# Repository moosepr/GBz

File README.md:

# GBz
pi zero based, gameboy style inteface board

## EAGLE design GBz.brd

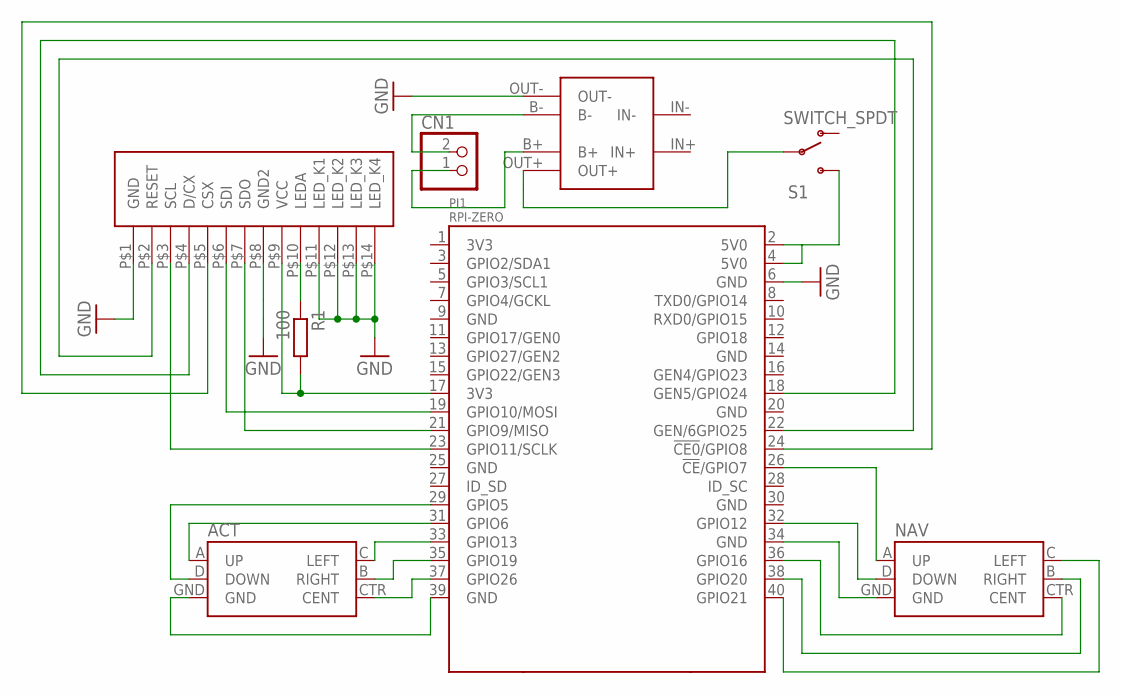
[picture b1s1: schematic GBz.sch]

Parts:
ACT: JOYSTICK_MINI
CN1: JST_2PIN-SMT-RA; JST-PH-2-SMT-RA
NAV: JOYSTICK_MINI
PI1: RPI-ZERO; RASPBERRYPI_BASTELSTUBE_V13_RASPI_BOARD_B+_FULL
POWER1: 03962A
R1: 100; R0805
S1: SWITCH_SPDT; KPS-1290
SCREEN1: ILI9341-2.2

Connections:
5V0@2: PI1.2 (5V0), PI1.4 (5V0), S1.S
GND: PI1.6 (GND), POWER1.OUT-, SCREEN1.P$1 (GND), SCREEN1.P$8 (GND2), SCREEN1.P$11 (LED_K1), SCREEN1.P$12 (LED_K2), SCREEN1.P$13 (LED_K3), SCREEN1.P$14 (LED_K4)
GND@3: ACT.GND, PI1.39 (GND)
GND@7: NAV.GND, PI1.34 (GND)
unnamed: PI1.22 (GEN/6GPIO25), SCREEN1.P$2 (RESET)
unnamed: PI1.23 (GPIO11/SCLK), SCREEN1.P$3 (SCL)
unnamed: PI1.19 (GPIO10/MOSI), SCREEN1.P$6 (SDI)
unnamed: PI1.21 (GPIO9/MISO), SCREEN1.P$7 (SDO)
unnamed: R1.1, SCREEN1.P$10 (LEDA)
unnamed: PI1.18 (GEN5/GPIO24), SCREEN1.P$4 (D/CX)
unnamed: PI1.24 (!CE0!/GPIO8), SCREEN1.P$5 (CSX)
unnamed: NAV.CTR (CENT), PI1.36 (GPIO16)
unnamed: ACT.CTR (CENT), PI1.37 (GPIO26)
unnamed: ACT.B (RIGHT), PI1.35 (GPIO19)
unnamed: ACT.C (LEFT), PI1.33 (GPIO13)
unnamed: ACT.A (UP), PI1.31 (GPIO6)
unnamed: ACT.D (DOWN), PI1.29 (GPIO5)
unnamed: NAV.B (RIGHT), PI1.38 (GPIO20)
unnamed: NAV.C (LEFT), PI1.40 (GPIO21)
unnamed: CN1.1 (2), POWER1.B+
unnamed: NAV.D (DOWN), PI1.32 (GPIO12)
unnamed: NAV.A (UP), PI1.26 (!CE!/GPIO7)
unnamed: PI1.17 (3V3), R1.2, SCREEN1.P$9 (VCC)
unnamed: CN1.2 (1), POWER1.B-
unnamed: POWER1.OUT+, S1.P

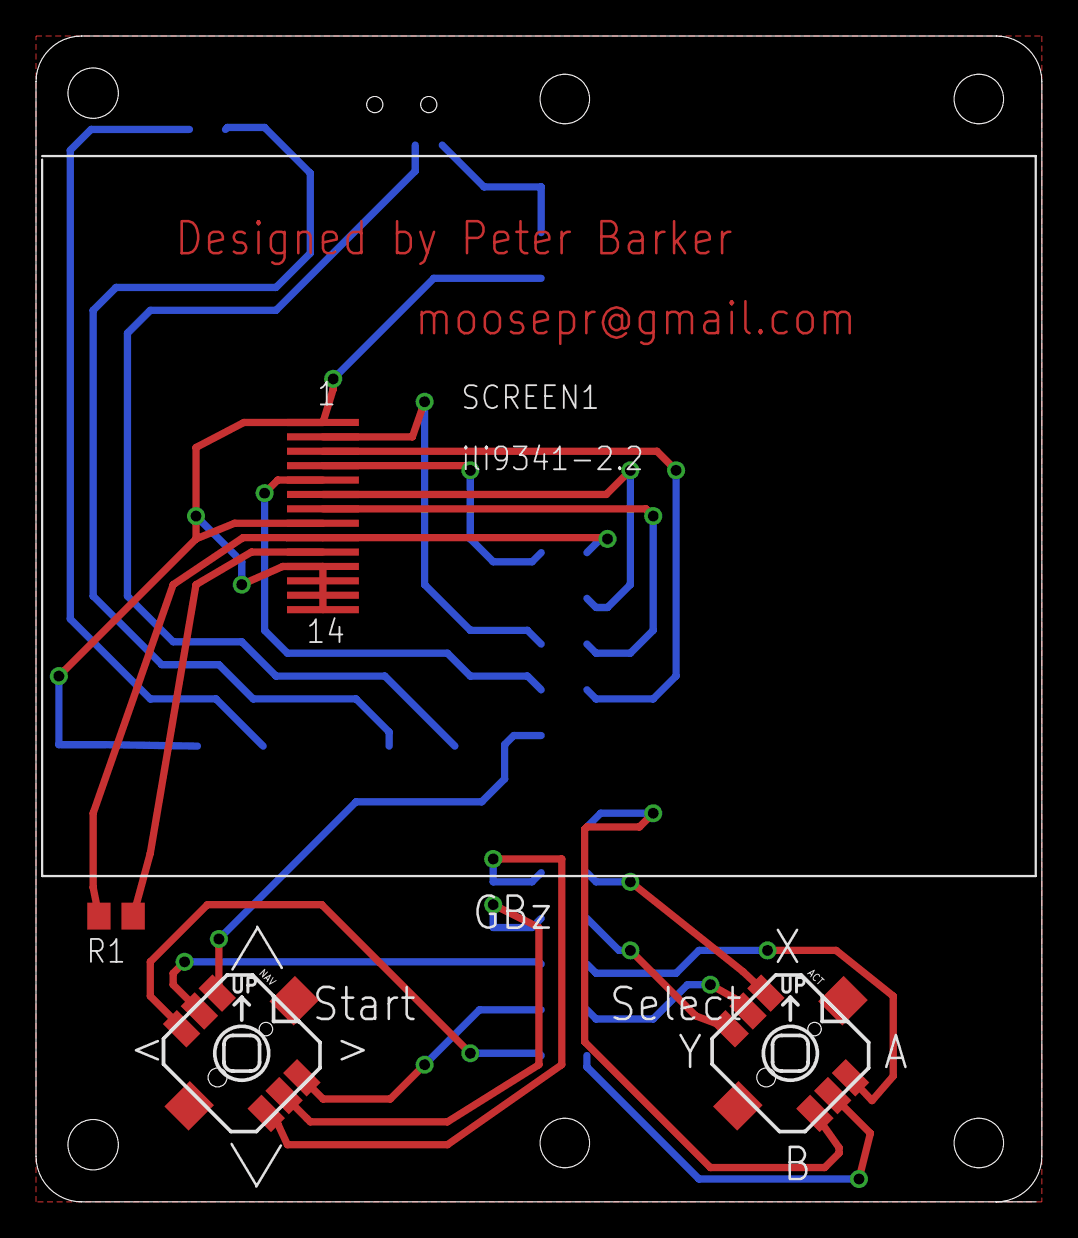
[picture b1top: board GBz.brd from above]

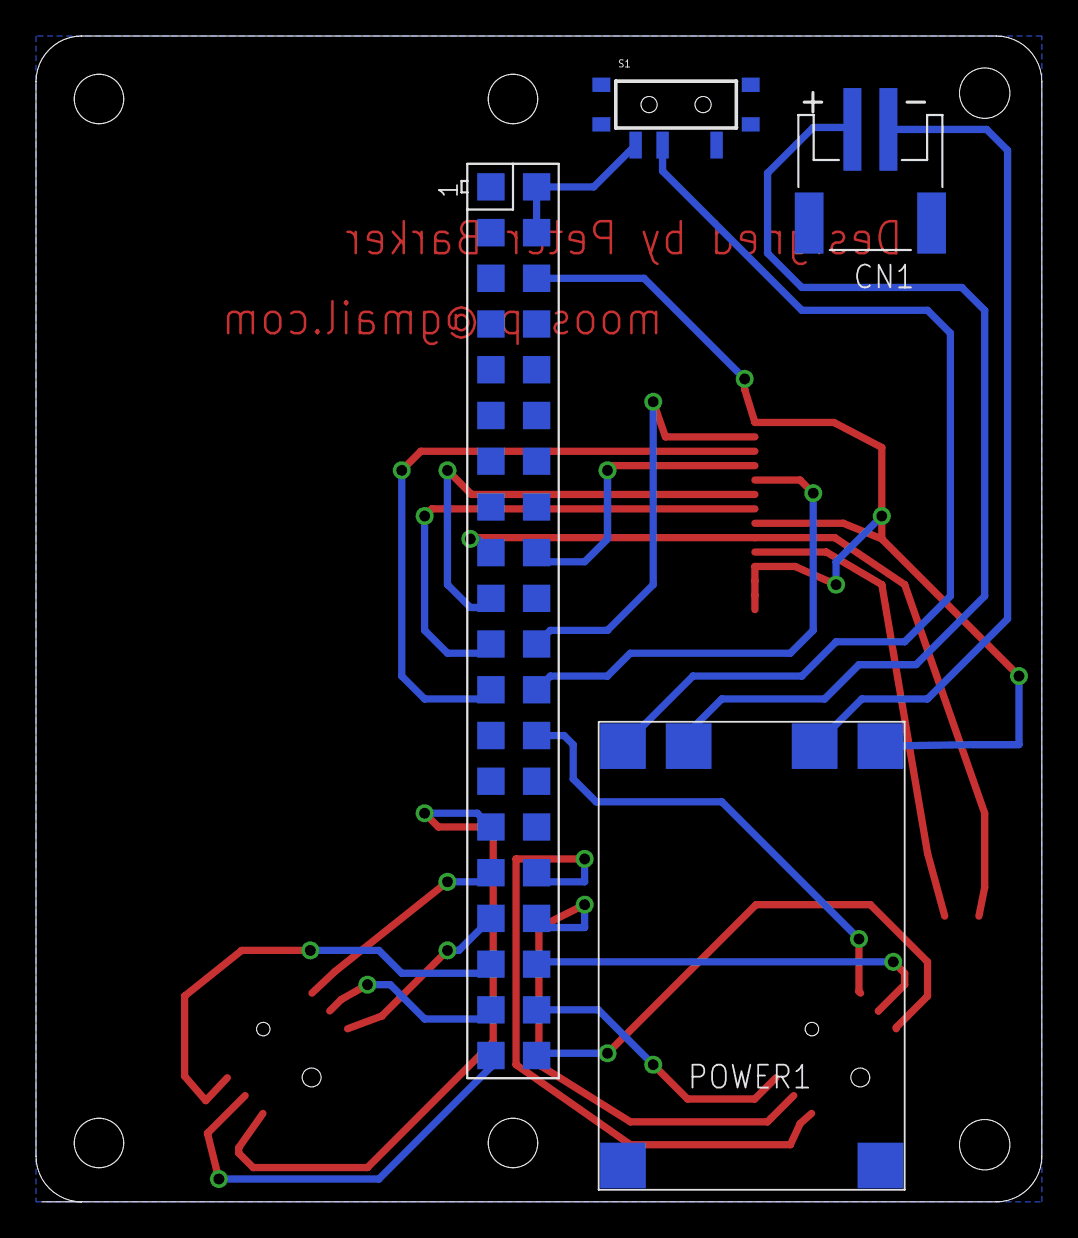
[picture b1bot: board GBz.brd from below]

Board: 2 copper layers, 55.9 x 64.8 mm, 8 parts (4 on the bottom side), 25 nets.

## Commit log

2017-01-30 inital files
    initial upload
2017-03-04 Add files via upload
    fixed the bad switch issue, rounded the corners, added some holes
2017-03-07 Add files via upload
    i think we are as far as we can go here!!

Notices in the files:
parts and their libraries:
SparkFun-Electromechanical: Licensing: Creative Commons ShareAlike 4.0 International - https://creativecommons.org/licenses/by-sa/4.0
